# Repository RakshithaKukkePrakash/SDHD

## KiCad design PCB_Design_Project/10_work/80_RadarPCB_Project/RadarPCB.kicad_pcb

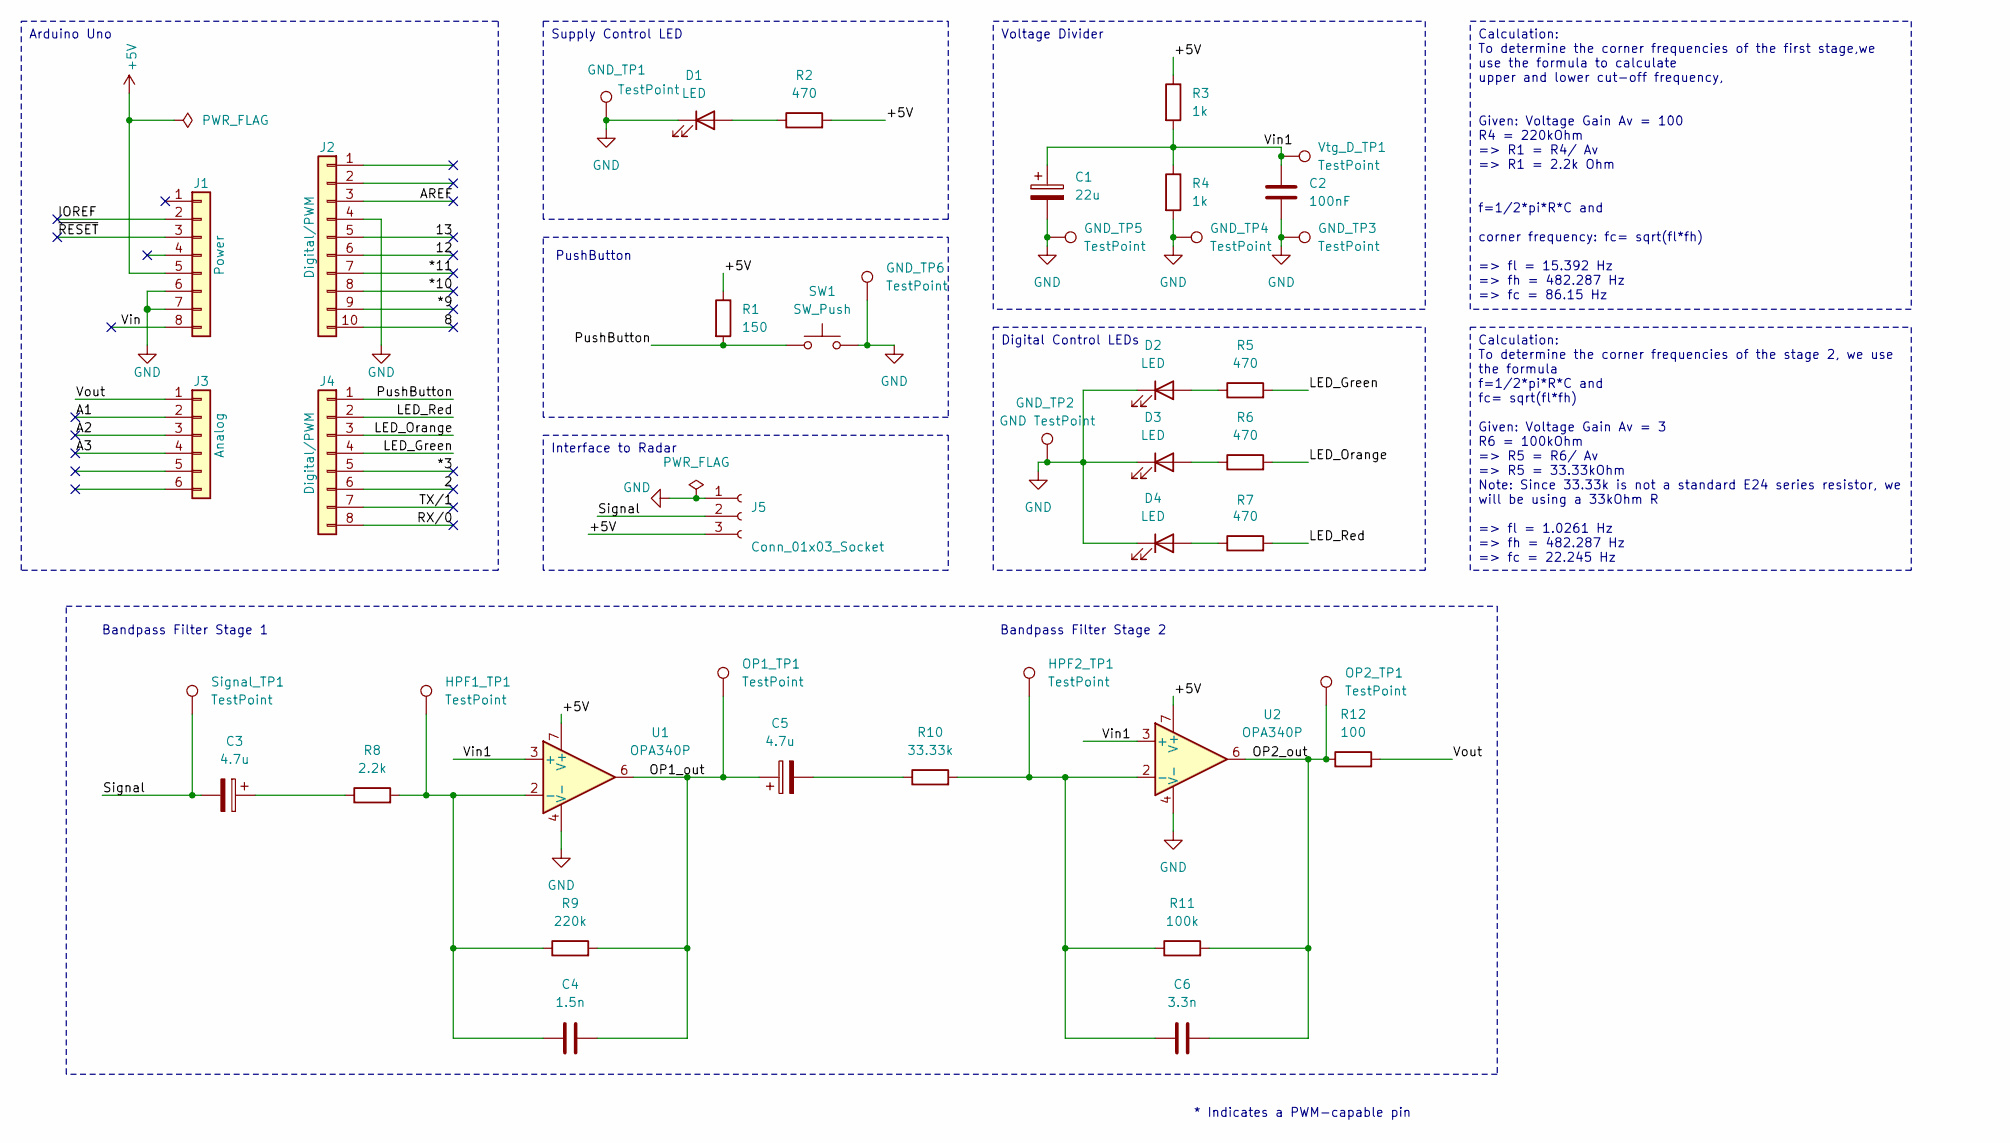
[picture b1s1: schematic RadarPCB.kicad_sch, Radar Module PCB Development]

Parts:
C1: 22u; C_Radial_D5.0mm_H11.0mm_P2.00mm
C2: 100nF; C_Rect_L7.2mm_W3.0mm_P5.00mm_FKS2_FKP2_MKS2_MKP2
C3, C5: 4.7u; C_Radial_D5.0mm_H11.0mm_P2.00mm
C4: 1.5n; C_Rect_L7.2mm_W4.5mm_P5.00mm_FKS2_FKP2_MKS2_MKP2
C6: 3.3n; C_Rect_L7.2mm_W4.5mm_P5.00mm_FKS2_FKP2_MKS2_MKP2
D1, D2, D3, D4: LED; LED_D5.0mm
GND_TP1, GND_TP3, GND_TP4, GND_TP5, GND_TP6: TestPoint; PinHeader_1x01_P2.54mm_Vertical
GND_TP2: GND TestPoint; PinHeader_1x01_P2.54mm_Vertical
HPF1_TP1, HPF2_TP1: TestPoint; PinHeader_1x01_P2.54mm_Vertical
J1: Power; PinHeader_1x08_P2.54mm_Vertical
J2: Digital/PWM; PinHeader_1x10_P2.54mm_Vertical
J3: Analog; PinHeader_1x06_P2.54mm_Vertical
J4: Digital/PWM; PinHeader_1x08_P2.54mm_Vertical
J5: Conn_01x03_Socket; PinSocket_1x03_P2.54mm_Horizontal
OP1_TP1, OP2_TP1: TestPoint; PinHeader_1x01_P2.54mm_Vertical
R1: 150; R_Axial_DIN0207_L6.3mm_D2.5mm_P10.16mm_Horizontal
R2, R5, R6, R7: 470; R_Axial_DIN0207_L6.3mm_D2.5mm_P10.16mm_Horizontal
R3, R4: 1k; R_Axial_DIN0207_L6.3mm_D2.5mm_P10.16mm_Horizontal
R8: 2.2k; R_Axial_DIN0207_L6.3mm_D2.5mm_P10.16mm_Horizontal
R9: 220k; R_Axial_DIN0207_L6.3mm_D2.5mm_P10.16mm_Horizontal
R10: 33.33k; R_Axial_DIN0207_L6.3mm_D2.5mm_P10.16mm_Horizontal
R11: 100k; R_Axial_DIN0207_L6.3mm_D2.5mm_P10.16mm_Horizontal
R12: 100; R_Axial_DIN0207_L6.3mm_D2.5mm_P10.16mm_Horizontal
SW1: SW_Push; SW_PUSH_6mm_H7.3mm
Signal_TP1: TestPoint; PinHeader_1x01_P2.54mm_Vertical
U1, U2: OPA340P; DIP-8_W7.62mm
Vtg_D_TP1: TestPoint; PinHeader_1x01_P2.54mm_Vertical

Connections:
+5V: J1.5, J5.3, R1.1, R2.2, R3.1, U1.7 (V+), U2.7 (V+)
/2: J4.6
/8: J2.10
/12: J2.6
/13: J2.5
/*3: J4.5
/*9: J2.9
/*10: J2.8
/*11: J2.7
/A1: J3.2
/A2: J3.3
/A3: J3.4
/AREF: J2.3
/IOREF: J1.2
/LED_Green: J4.4, R5.2
/LED_Orange: J4.3, R6.2
/LED_Red: J4.2, R7.2
/OP1_out: C4.2, C5.1, OP1_TP1.1, R9.2, U1.6
/OP2_out: C6.2, OP2_TP1.1, R11.2, R12.1, U2.6
/PushButton: J4.1, R1.2, SW1.1
/RX/0: J4.8
/Signal: C3.2, J5.2, Signal_TP1.1
/TX/1: J4.7
/Vin: J1.8
/Vin1: C1.1, C2.1, R3.2, R4.1, U1.3 (+), U2.3 (+), Vtg_D_TP1.1; also elsewhere on the board
/Vout: J3.1, R12.2
/~RESET: J1.3
GND: C1.2, C2.2, D1.1 (K), D2.1 (K), D3.1 (K), D4.1 (K), GND_TP1.1, GND_TP2.1, GND_TP3.1, GND_TP4.1, GND_TP5.1, GND_TP6.1, J1.6, J1.7, J2.4, J5.1, R4.2, SW1.2, U1.4 (V-), U2.4 (V-)
unnamed: C3.1, R8.1
unnamed: C5.2, R10.1
unnamed: D1.2 (A), R2.1
unnamed: D2.2 (A), R5.1
unnamed: D3.2 (A), R6.1
unnamed: D4.2 (A), R7.1
unnamed 34: C4.1, HPF1_TP1.1, R8.2, R9.1, U1.2 (-); also elsewhere on the board
unnamed 35: C6.1, HPF2_TP1.1, R10.2, R11.1, U2.2 (-); also elsewhere on the board

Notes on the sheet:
Calculation: To determine the corner frequencies of the stage 2, we use the formula f=1/2*pi*R*C and fc= sqrt(fl*fh) Given: Voltage Gain Av = 3 R6 = 100kOhm => R5 = R6/ Av => R5 = 33.33kOhm Note: Since 33.33k is not a standard E24 series resistor, we will be using a 33kOhm R => fl = 1.0261 Hz => fh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
Voltage Divider
Interface to Radar
Supply Control LED
Arduino Uno
Calculation: To determine the corner frequencies of the first stage,we use the formula to calculate upper and lower cut-off frequency, Given: Voltage Gain Av = 100 R4 = 220kOhm => R1 = R4/ Av => R1 = 2.2k Ohm f=1/2*pi*R*C and corner frequency: fc= sqrt(fl*fh) => fl = 15.392 Hz => fh = 482.287 Hz =>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
Digital Control LEDs
Bandpass Filter Stage 2
* Indicates a PWM-capable pin
PushButton
Bandpass Filter Stage 1

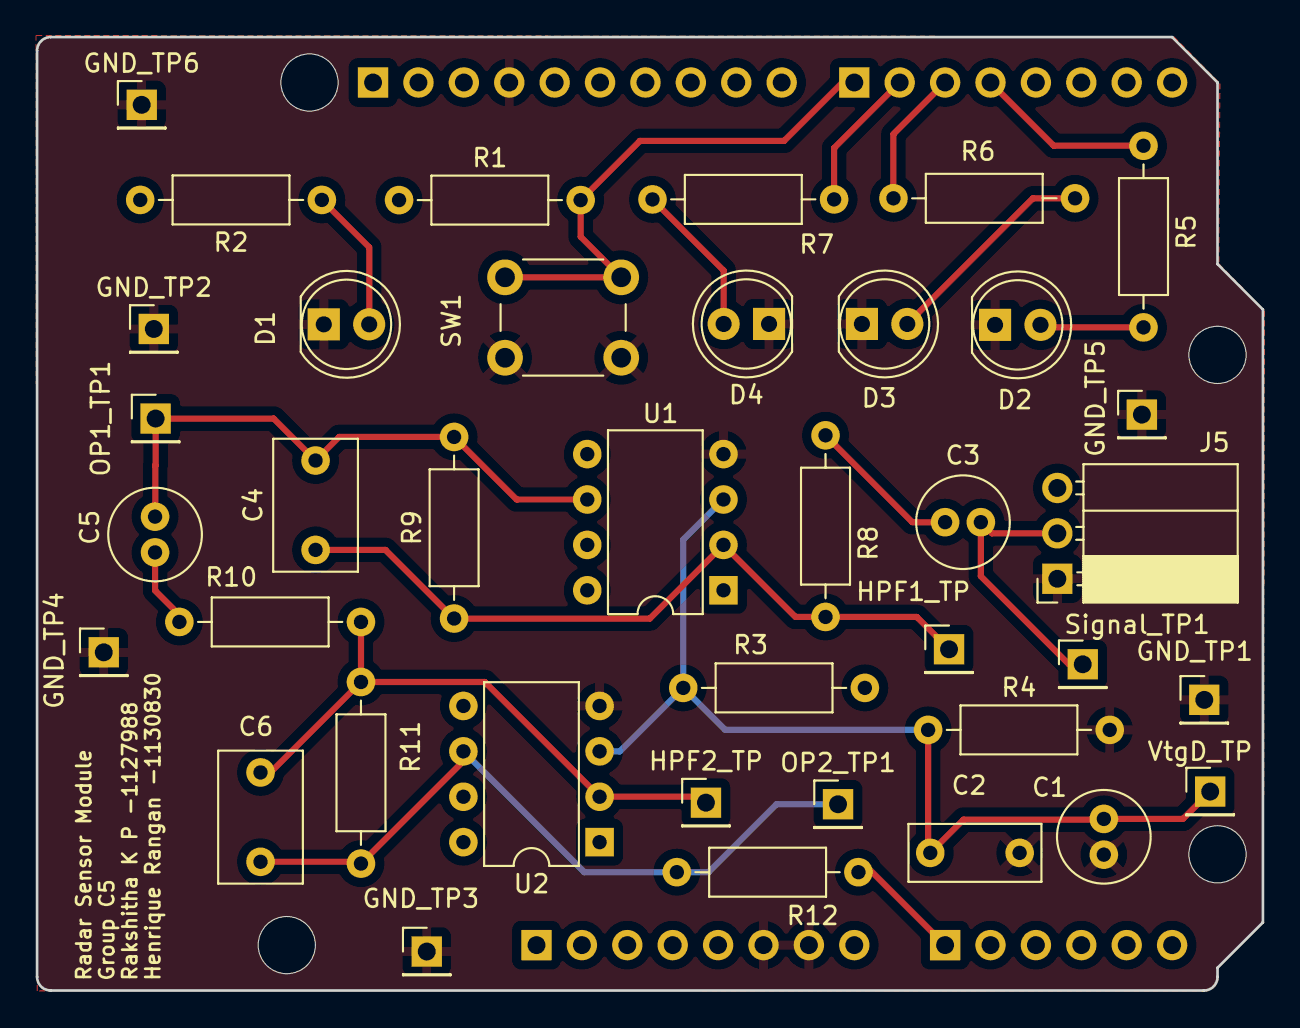
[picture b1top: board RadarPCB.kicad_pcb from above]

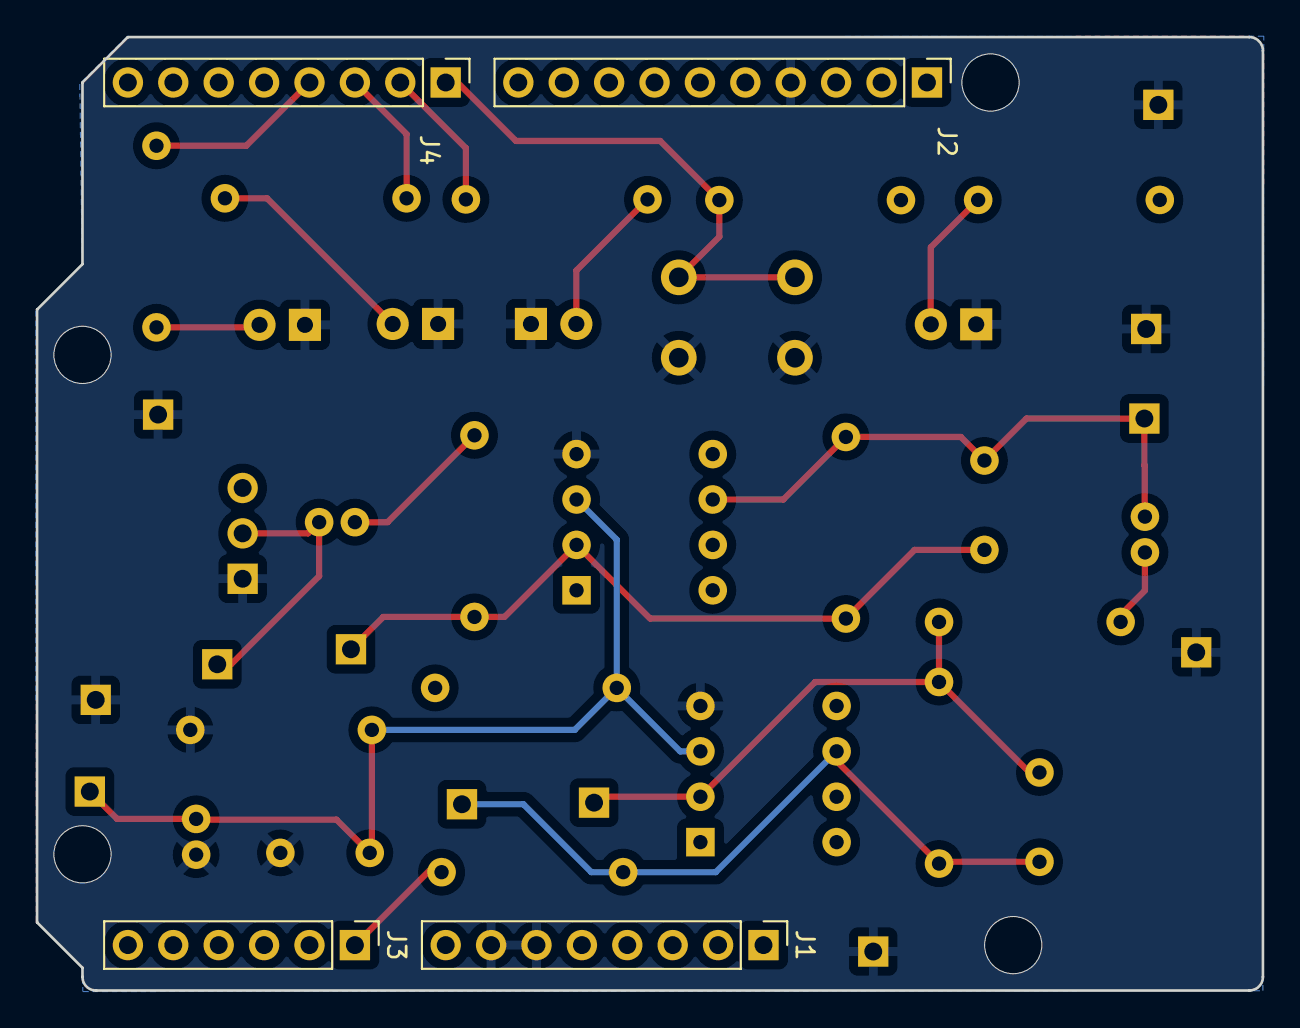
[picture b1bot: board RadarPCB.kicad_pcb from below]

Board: 4 copper layers, 68.6 x 53.3 mm, 46 parts (4 on the bottom side), 19 nets.

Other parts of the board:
HPF1_TP, HPF2_TP: TestPoint; PinHeader_1x01_P2.54mm_Vertical
MH1, MH2, MH3, MH4: MountingHole_3.2mm
VtgD_TP: TestPoint; PinHeader_1x01_P2.54mm_Vertical

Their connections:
/Vin1: VtgD_TP.1; also elsewhere on the board
unnamed 34: HPF1_TP.1; also elsewhere on the board
unnamed 35: HPF2_TP.1; also elsewhere on the board

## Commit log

2024-06-02 Exercise1-2
    PSoC exercise to talk back and capitalize message tx through UART
2024-06-02 PCB design
    pcb schematic and layout for radar module
2024-06-02 Datatransfer from FreeSoc2 to Matlab
    Datatransfer from FreeSoc2 to Matlab
2024-06-02 Ex123
    Exercises complete
2024-06-04 Lab3
    Initial PSoC setup for lab3 ie DAC; ADC added
2024-06-05 State machine
    state machine started
2024-06-13 Lab3 with MATLAB fft
    Lab3 with MATLAB fft
2024-06-18 ADC done
    ADC fft from matlab
2024-06-18 FFT complete
    Complete - backup
2024-06-19 All done
    DONE
2024-07-16 Final PPT
    ppt
2024-07-16 Matlab scripts
    Matlab scripts
2024-07-16 PSocWithout cfar
    PSoc Without cfar
